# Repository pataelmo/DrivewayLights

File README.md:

# DrivewayLights
This is a project to create smart IoT driveway lights.

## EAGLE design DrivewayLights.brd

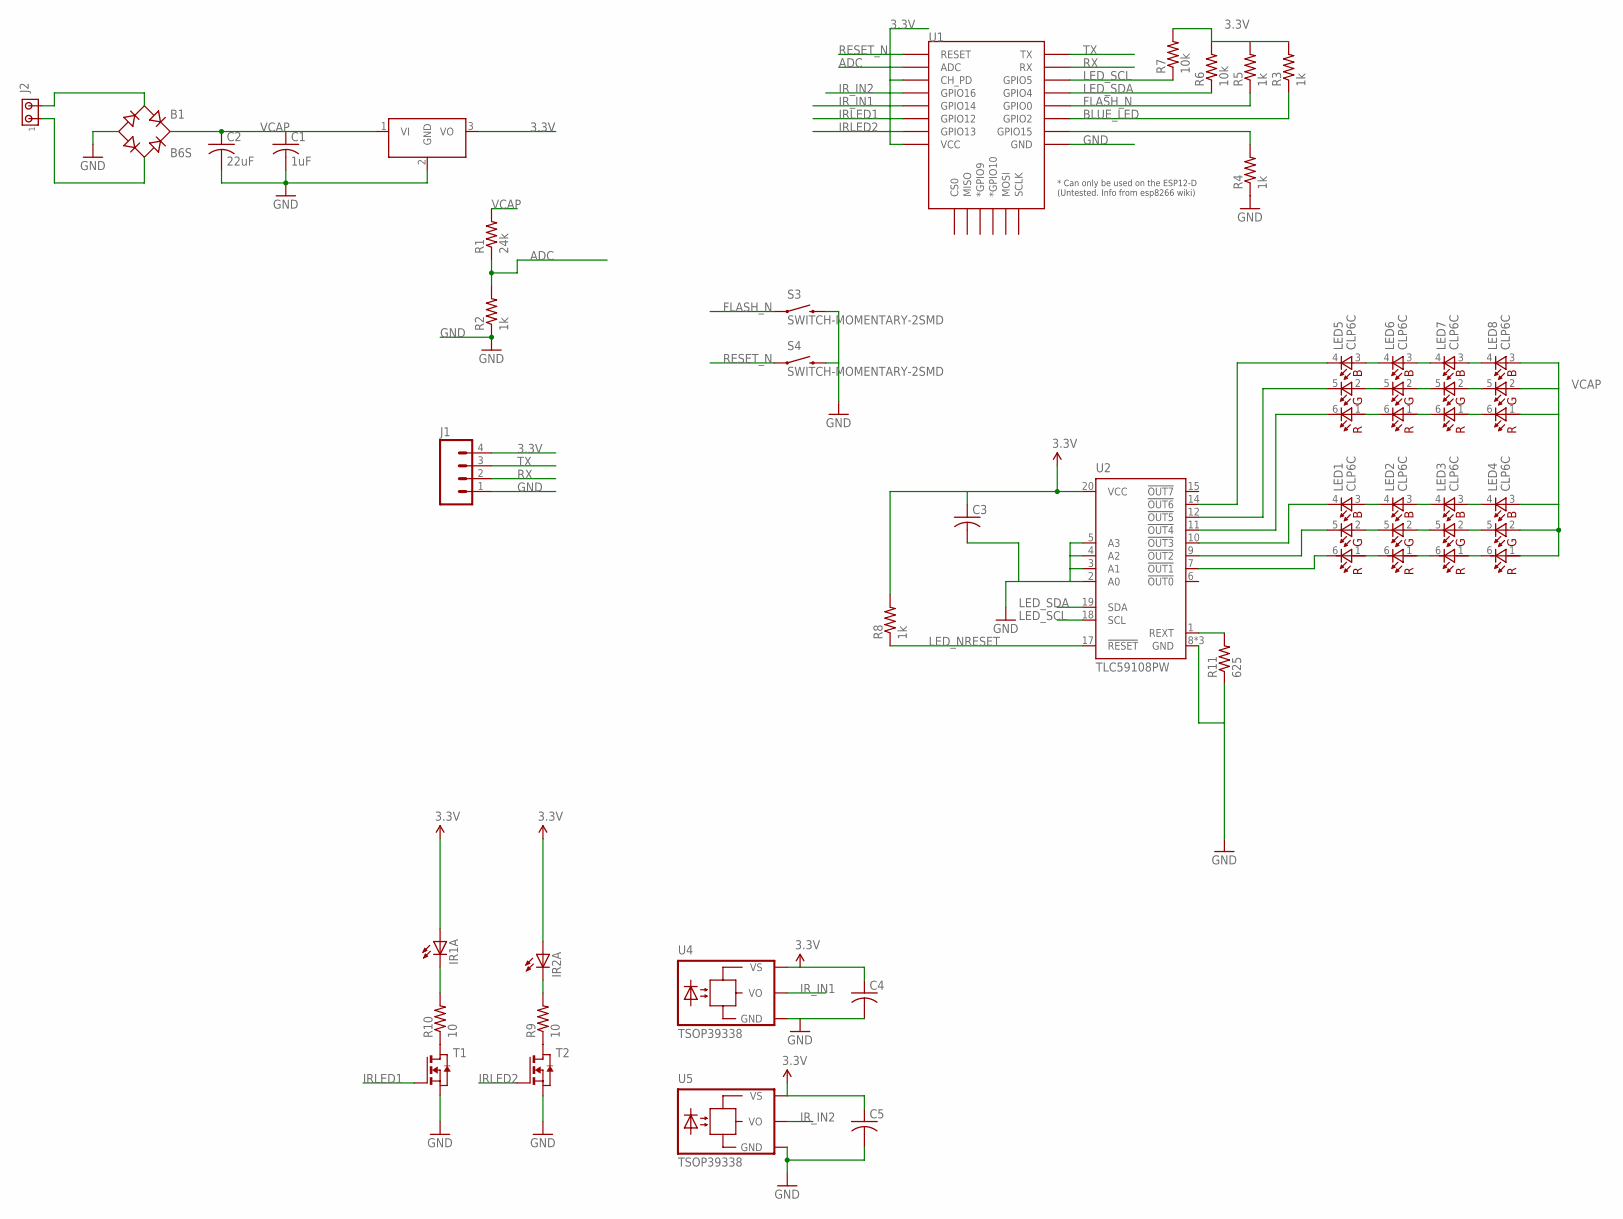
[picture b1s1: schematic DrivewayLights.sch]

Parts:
B1: B6S; MBS
C1: 1uF; C0805
C2: 22uF; C1210
C3, C4, C5: C-USC0603; C0603
IR1A, IR2A: LED5MM
J1: M04JST-PTH-VERT; JST-4-PTH-VERT
J2: MTA02-100; 10X02MTA
LED1, LED2, LED3, LED4, LED5, LED6, LED7, LED8: CLP6C
R1: 24k; R0603
R2, R3, R4, R5, R8: 1k; R0603
R6, R7: 10k; R0603
R9, R10: 10; R0603
R11: 625; R0603
S3, S4: SWITCH-MOMENTARY-2SMD; TACTILE-SWITCH-SMD
T1, T2: NMOSSOT23; SOT-23
U1: ESP12ESMD; ESP12E-SMD
U2: TLC59108PW; PW_R-PDSO-G20
U3: DCDC_OKI-78SR; OKI-78SRH
U4, U5: TSOP39338

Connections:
3.3V: C3.1, C4.1, C5.1, IR1A.A, IR2A.A, J1.4, R3.2, R5.2, R6.2, R7.2, R8.2, U1.CH_PD, U1.VCC, U2.20 (VCC), U3.3 (VO), U4.VS, U5.VS
ADC: R1.1, R2.2, U1.ADC
BLUE: LED1.4 (BC), U2.10 (!OUT3)
BLUE2: LED5.4 (BC), U2.14 (!OUT6)
BLUE_LED: R3.1, U1.GPIO2
FLASH_N: R5.1, S3.1, U1.GPIO0
GND: B1.-, C1.2, C2.2, C3.2, C4.2, C5.2, J1.1, R2.1, R4.1, R11.1, S3.3 (2), S4.3 (2), T1.2 (S), T2.2 (S), U1.GND, U2.2 (A0), U2.3 (A1), U2.4 (A2), U2.5 (A3), U2.8 (GND), U2.13 (GND), U2.16 (GND), U3.2 (GND), U4.GND, U5.GND
GREEN: LED1.5 (GC), U2.9 (!OUT2)
GREEN2: LED5.5 (GC), U2.12 (!OUT5)
IRLED0: R4.2, U1.GPIO15
IRLED1: T1.3 (G), U1.GPIO12
IRLED2: T2.3 (G), U1.GPIO13
IR_IN1: U1.GPIO14, U4.OUT (VO)
IR_IN2: U1.GPIO16, U5.OUT (VO)
LED_CURRENT_R: R11.2, U2.1 (REXT)
LED_NRESET: R8.1, U2.17 (!RESET)
LED_SCL: R7.1, U1.GPIO5, U2.18 (SCL)
LED_SDA: R6.1, U1.GPIO4, U2.19 (SDA)
unnamed: IR2A.K (C), R9.2
unnamed: IR1A.K (C), R10.2
unnamed: R10.1, T1.1 (D)
unnamed: R9.1, T2.1 (D)
unnamed: LED5.3 (BA), LED6.4 (BC)
unnamed: LED6.3 (BA), LED7.4 (BC)
unnamed: LED7.3 (BA), LED8.4 (BC)
unnamed: LED7.2 (GA), LED8.5 (GC)
unnamed: LED6.2 (GA), LED7.5 (GC)
unnamed: LED5.2 (GA), LED6.5 (GC)
unnamed: LED5.1 (RA), LED6.6 (RC)
unnamed: LED6.1 (RA), LED7.6 (RC)
unnamed: LED7.1 (RA), LED8.6 (RC)
unnamed: LED1.3 (BA), LED2.4 (BC)
unnamed: LED2.3 (BA), LED3.4 (BC)
unnamed: LED3.3 (BA), LED4.4 (BC)
unnamed: LED3.2 (GA), LED4.5 (GC)
unnamed: LED2.2 (GA), LED3.5 (GC)
unnamed: LED1.2 (GA), LED2.5 (GC)
unnamed: LED1.1 (RA), LED2.6 (RC)
unnamed: LED2.1 (RA), LED3.6 (RC)
unnamed: LED3.1 (RA), LED4.6 (RC)
unnamed: B1.AC1, J2.2
unnamed: B1.AC2, J2.1
RED: LED1.6 (RC), U2.7 (!OUT1)
RED2: LED5.6 (RC), U2.11 (!OUT4)
RESET_N: S4.1, U1.RESET
RX: J1.2, U1.RXD0 (RX)
TX: J1.3, U1.TXD0 (TX)
VCAP: B1.+, C1.1, C2.1, LED4.1 (RA), LED4.2 (GA), LED4.3 (BA), LED8.1 (RA), LED8.2 (GA), LED8.3 (BA), R1.2, U3.1 (VI)

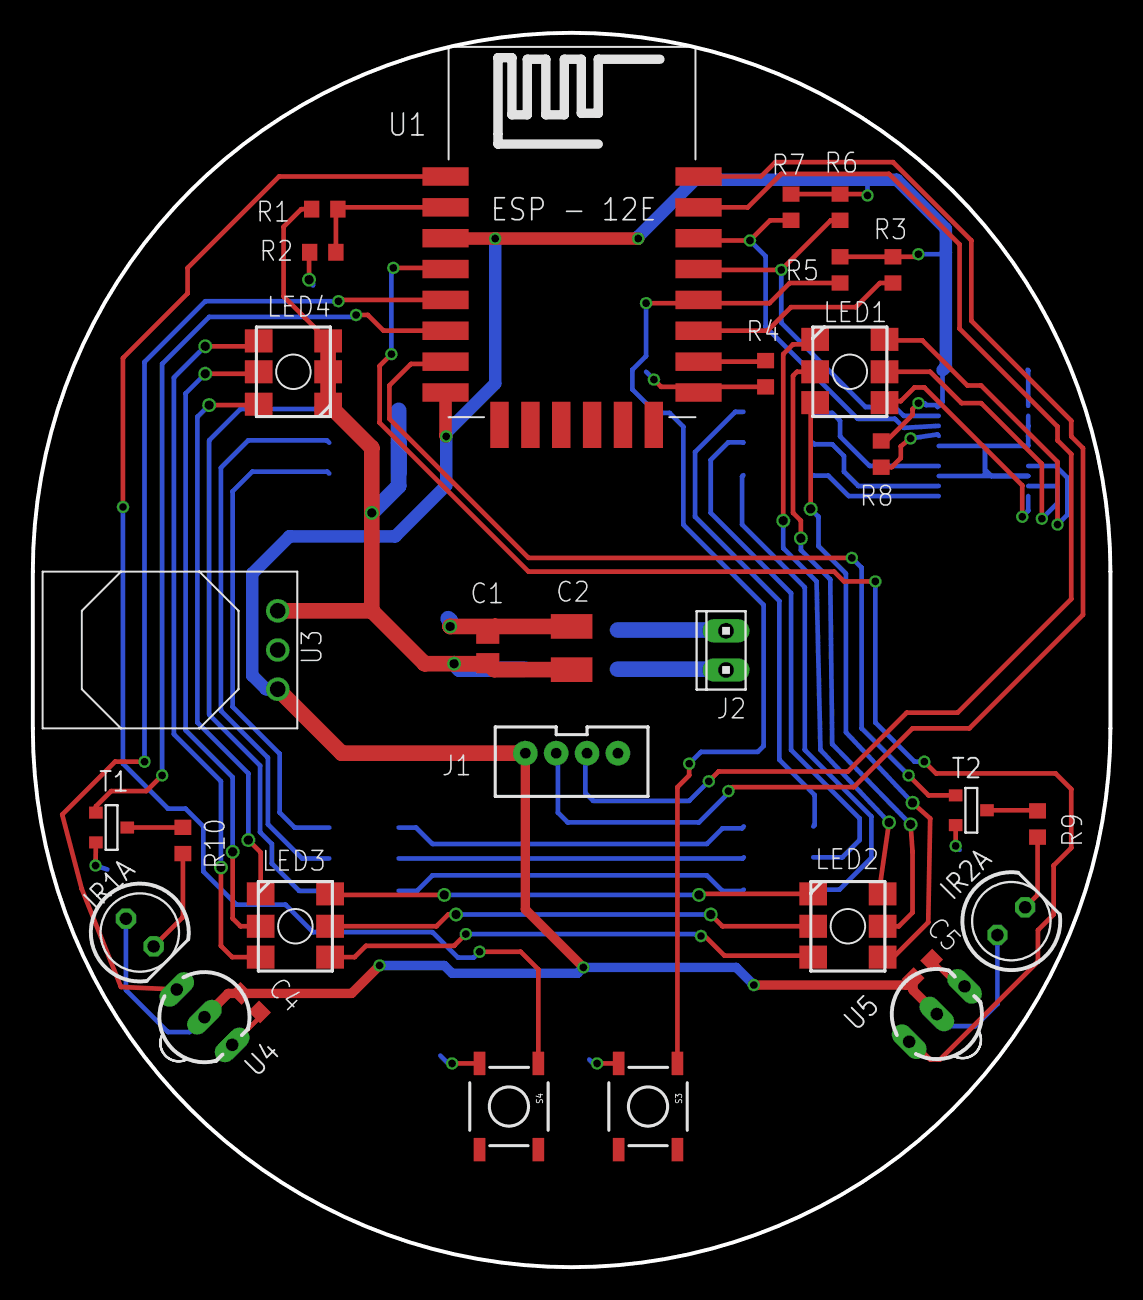
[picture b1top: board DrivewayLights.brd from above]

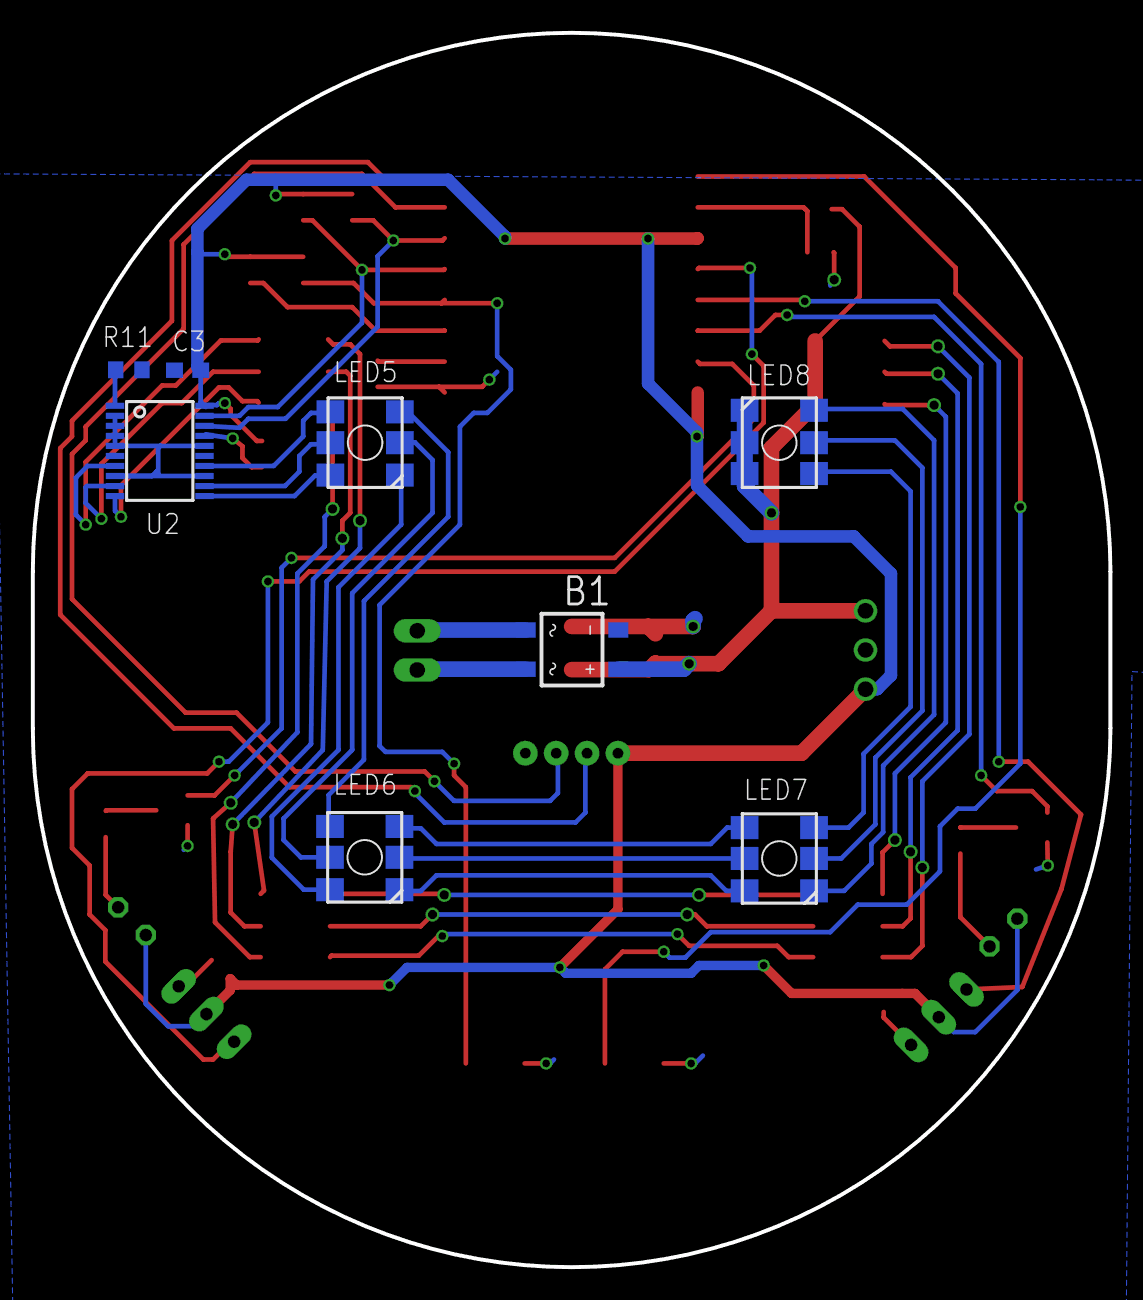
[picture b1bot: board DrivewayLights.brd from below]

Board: 2 copper layers, 69.8 x 80.0 mm, 38 parts (8 on the bottom side), 48 nets.

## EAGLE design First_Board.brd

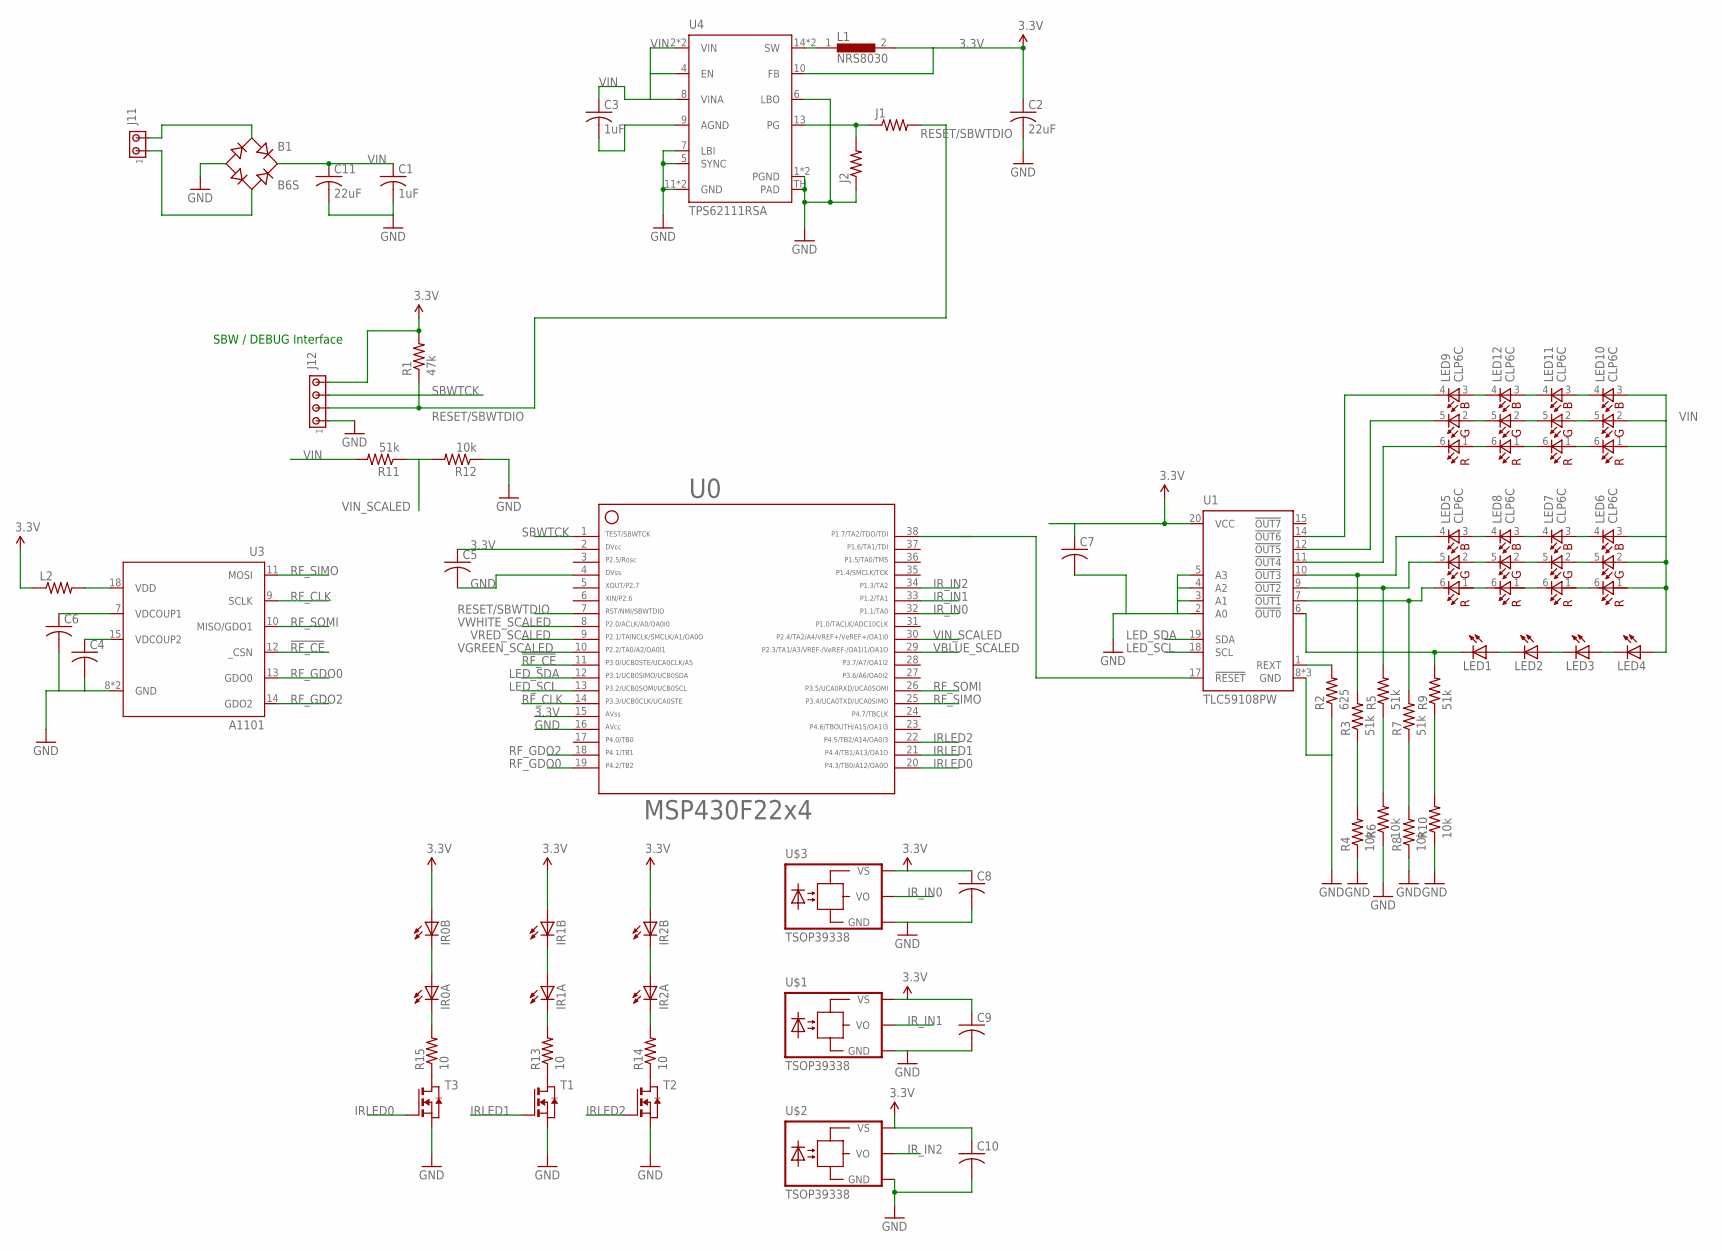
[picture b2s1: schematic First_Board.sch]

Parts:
B1: B6S; MBS
C1: 1uF; C0805
C2: 22uF; C0805
C3: 1uF; C0603
C4, C5, C6, C7, C8, C9, C10: C-USC0603; C0603
C11: 22uF; C1210
IR0A, IR0B, IR1A, IR1B, IR2A, IR2B: LED5MM
J1, J2: R-US_R0603; R0603
J11: MTA02-100; 10X02MTA
J12: MTA04-100; 10X04MTA
L1: NRS8030
L2: R-US_R0603; R0603
LED1, LED2, LED3, LED4: LED-2AC-SUPERFLUX; SUPERFLUX-7.6X7.6
LED5, LED6, LED7, LED8, LED9, LED10, LED11, LED12: CLP6C
R1: 47k; R0603
R2: 625; R0603
R3, R5, R7, R9, R11: 51k; R0603
R4, R6, R8, R10, R12: 10k; R0603
R13, R14, R15: 10; R0603
T1, T2, T3: NMOSSOT23; SOT-23
U0: F22X4---DA38; DA38
U1: TLC59108PW; PW_R-PDSO-G20
U3: A1101
U4: TPS62111RSA; S-PVQFN-N16
U$1, U$2, U$3: TSOP39338

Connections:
3.3V: C2.1, C5.1, C7.1, C8.1, C9.1, C10.1, IR0B.A, IR1B.A, IR2B.A, J12.4, L1.2, L2.1, R1.2, U0.2, U0.15, U1.20 (VCC), U4.10 (FB), U$1.VS, U$2.VS, U$3.VS
!RF_CE: U0.11, U3.12 (_CSN)
BLUE: LED5.4 (BC), R3.2, U1.10 (!OUT3)
BLUE2: LED9.4 (BC), U1.14 (!OUT6)
GND: B1.-, C1.2, C2.2, C4.2, C5.2, C6.2, C7.2, C8.2, C9.2, C10.2, C11.2, J2.1, J12.1, R2.1, R4.1, R6.1, R8.1, R10.1, R12.1, T1.2 (S), T2.2 (S), T3.2 (S), U0.4, U0.16, U1.2 (A0), U1.3 (A1), U1.4 (A2), U1.5 (A3), U1.8 (GND), U1.13 (GND), U1.16 (GND), U3.8 (GND), U3.17 (GND), U4.1 (PGND), U4.5 (SYNC), U4.6 (LBO), U4.7 (LBI), U4.11 (GND), U4.12 (GND), U4.16 (PGND), U4.TH (PAD), U$1.GND, U$2.GND, U$3.GND
GREEN: LED5.5 (GC), R5.2, U1.9 (!OUT2)
GREEN2: LED9.5 (GC), U1.12 (!OUT5)
IRLED0: T3.3 (G), U0.20
IRLED1: T1.3 (G), U0.21
IRLED2: T2.3 (G), U0.22
IR_IN0: U0.32, U$3.OUT (VO)
IR_IN1: U0.33, U$1.OUT (VO)
IR_IN2: U0.34, U$2.OUT (VO)
LED_SCL: U0.13, U1.18 (SCL)
LED_SDA: U0.12, U1.19 (SDA)
unnamed: L1.1, U4.14 (SW), U4.15 (SW)
unnamed: IR2A.K (C), R14.2
unnamed: IR2A.A, IR2B.K (C)
unnamed: IR1A.A, IR1B.K (C)
unnamed: IR1A.K (C), R13.2
unnamed: R13.1, T1.1 (D)
unnamed: C3.2, U4.9 (AGND)
unnamed: R14.1, T2.1 (D)
unnamed: LED1.1 (C), LED1.3 (C), R9.2, U1.6 (!OUT0)
unnamed: LED9.3 (BA), LED12.4 (BC)
unnamed: LED11.4 (BC), LED12.3 (BA)
unnamed: LED10.4 (BC), LED11.3 (BA)
unnamed: LED10.5 (GC), LED11.2 (GA)
unnamed: LED11.5 (GC), LED12.2 (GA)
unnamed: LED9.2 (GA), LED12.5 (GC)
unnamed: LED9.1 (RA), LED12.6 (RC)
unnamed: R2.2, U1.1 (REXT)
unnamed: LED11.6 (RC), LED12.1 (RA)
unnamed: LED10.6 (RC), LED11.1 (RA)
unnamed: IR0A.K (C), R15.2
unnamed: IR0A.A, IR0B.K (C)
unnamed: R15.1, T3.1 (D)
unnamed: LED5.3 (BA), LED8.4 (BC)
unnamed: LED7.4 (BC), LED8.3 (BA)
unnamed: LED6.4 (BC), LED7.3 (BA)
unnamed: LED6.5 (GC), LED7.2 (GA)
unnamed: LED7.5 (GC), LED8.2 (GA)
unnamed: LED5.2 (GA), LED8.5 (GC)
unnamed: LED5.1 (RA), LED8.6 (RC)
unnamed: LED7.6 (RC), LED8.1 (RA)
unnamed: LED6.6 (RC), LED7.1 (RA)
unnamed: LED1.2 (A), LED1.4 (A), LED2.1 (C), LED2.3 (C)
unnamed: LED2.2 (A), LED2.4 (A), LED3.1 (C), LED3.3 (C)
unnamed: LED3.2 (A), LED3.4 (A), LED4.1 (C), LED4.3 (C)
unnamed: B1.AC1, J11.2
unnamed: B1.AC2, J11.1
unnamed: L2.2, U3.18 (VDD)
PG: J1.1, J2.2, U4.13 (PG)
RED: LED5.6 (RC), R7.2, U1.7 (!OUT1)
RED2: LED9.6 (RC), U1.11 (!OUT4)
RESET/SBWTDIO: J1.2, J12.2, R1.1, U0.7
RF_CLK: U0.14, U3.9 (SCLK)
RF_GDO0: U0.19, U3.13 (GDO0)
RF_GDO2: U0.18, U3.14 (GDO2)
RF_SIMO: U0.25, U3.11 (MOSI)
RF_SOMI: U0.26, U3.10 (MISO/GDO1)
SBWTCK: J12.3, U0.1
VBLUE_SCALED: R3.1, R4.2, U0.29
VDCOUP1: C6.1, U3.7 (VDCOUP1)
VDCOUP2: C4.1, U3.15 (VDCOUP2)
VGREEN_SCALED: R5.1, R6.2, U0.10
VIN: B1.+, C1.1, C3.1, C11.1, LED4.2 (A), LED4.4 (A), LED6.1 (RA), LED6.2 (GA), LED6.3 (BA), LED10.1 (RA), LED10.2 (GA), LED10.3 (BA), R11.2, U4.2 (VIN), U4.3 (VIN), U4.4 (EN), U4.8 (VINA)
VIN_SCALED: R11.1, R12.2, U0.30
VRED_SCALED: R7.1, R8.2, U0.9
VWHITE_SCALED: R9.1, R10.2, U0.8

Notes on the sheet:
SBW / DEBUG Interface

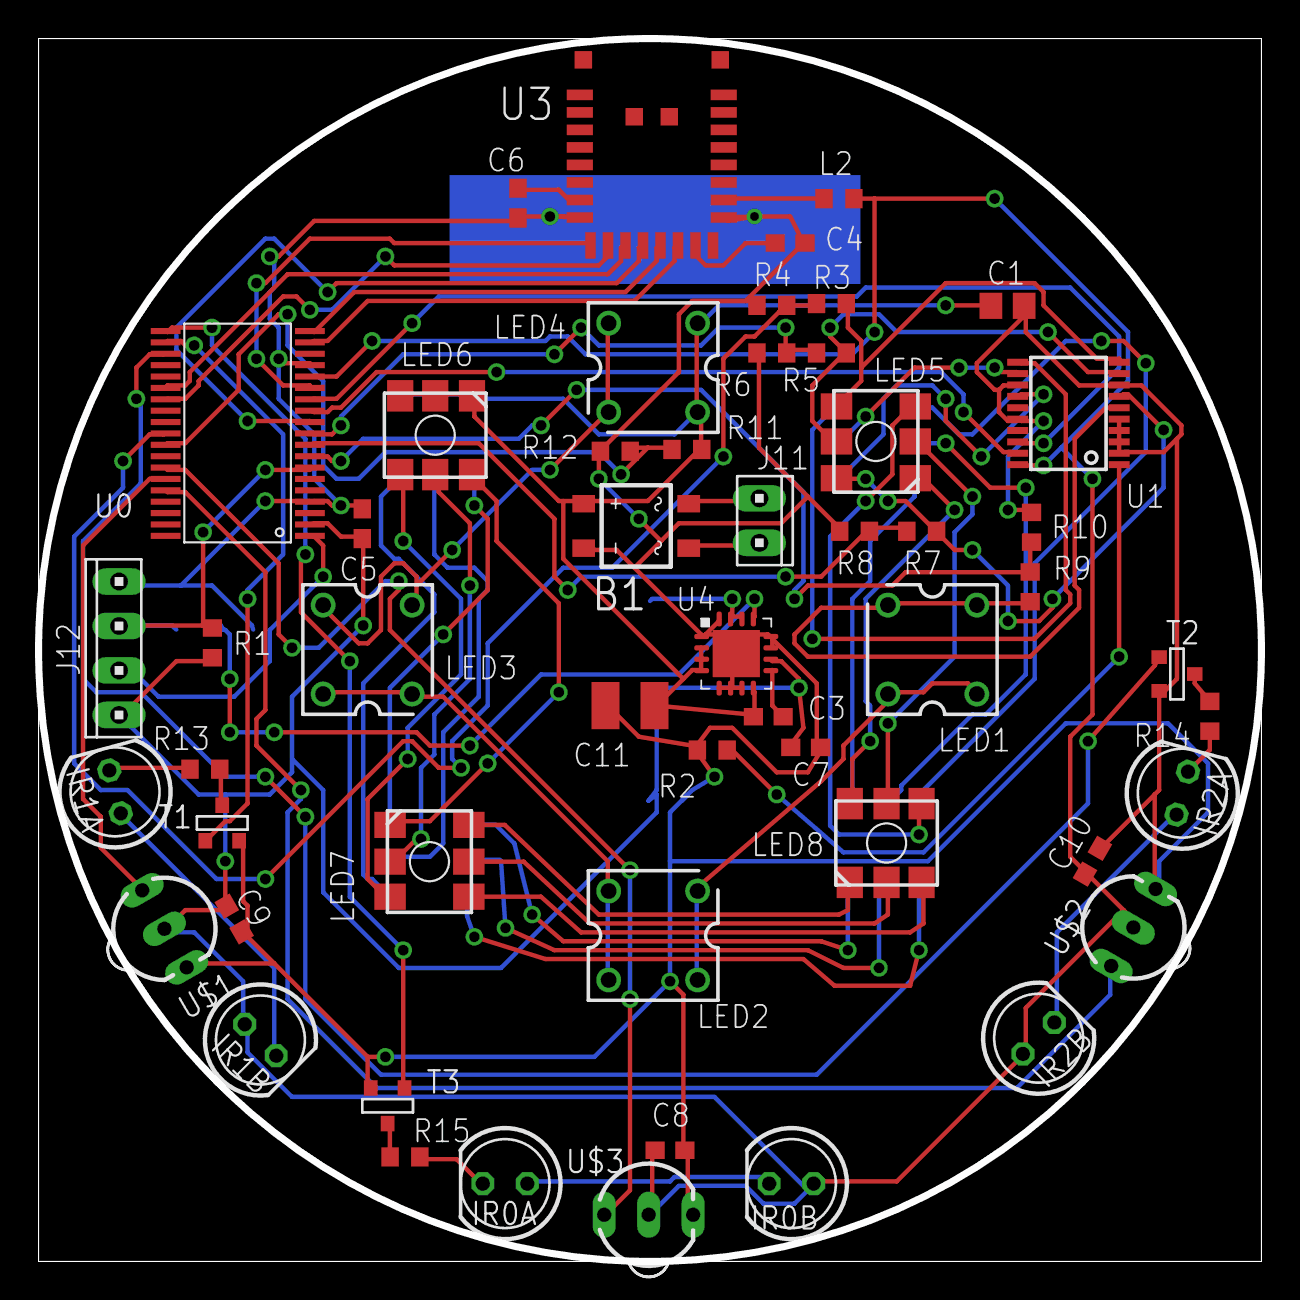
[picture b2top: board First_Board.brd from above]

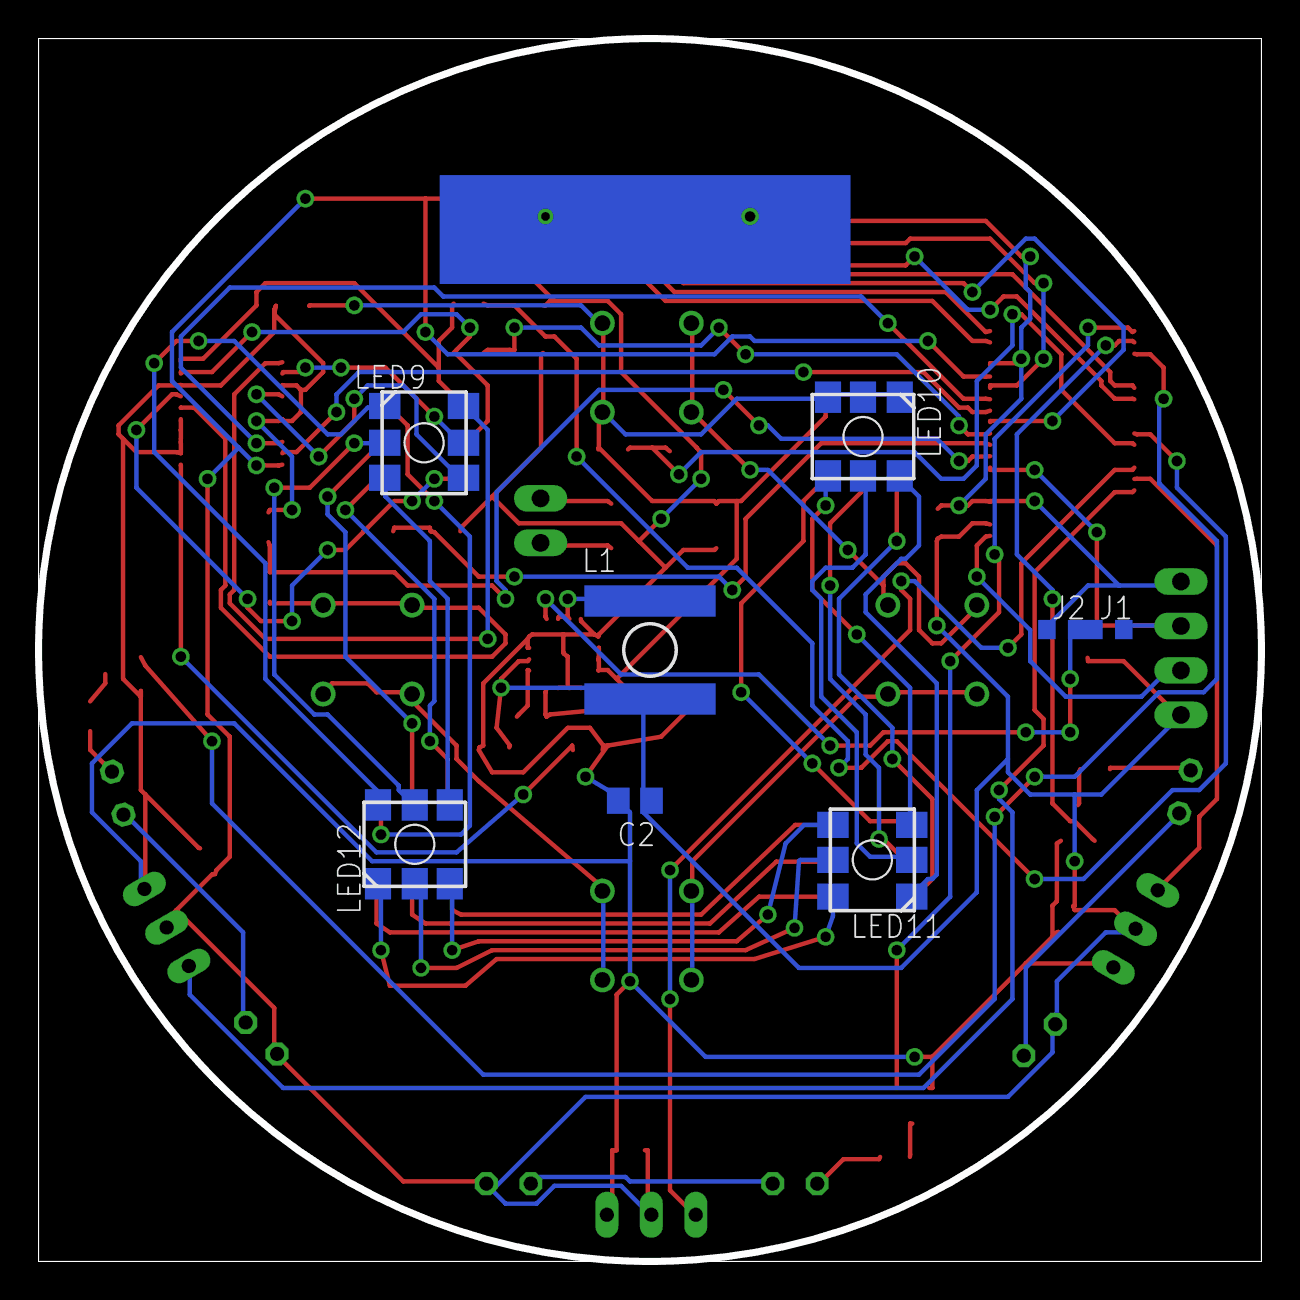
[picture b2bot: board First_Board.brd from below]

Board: 2 copper layers, 69.9 x 69.9 mm, 61 parts (8 on the bottom side), 70 nets.

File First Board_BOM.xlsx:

Designator | Type | Value | Part # | Package |  | ORDER
J11 | Connector | Power In |  | 2 Pin |  | ???
B1 | Bridge | - | B6S
C11 | Capacitor | 22uF |  | 1210
C1 | Capacitor | 1uF |  | 0805
U4 | IC | - | TPS62111RSA | PVQFN-16
C3 | Capacitor | 1uF |  | 0603
L1 | Inductor | - | NRS8030
J1/J2 | Resistor | 0 |  | 0603
C2 | Capacitor | 22uF |  | 0805
J12 | Connector | JTAG |  | 4 Pin
R1 | Resistor | 47k |  | 0603
R11 | Resistor | 51k |  | 0603
R12 | Resistor | 10k |  | 0603
U3 | Module | - | A1101
L2 | Inductor | - |  | 0603 |  | 0 ohm
C6 | Capacitor | - |  | 0603 |  | NO
C4 | Capacitor | - |  | 0603 |  | NO
U0 | IC | - | MSP430F2274 | DA38?
C5 | Capacitor | 1uF |  | 0603 |  | 1uF
U1 | IC | - | TLC59108PW
C7 | Capacitor | 1uF |  | 0603 |  | 1uF
R2 | Resistor | 625 |  | 0603
R3 | Resistor | 51k |  | 0603
R4 | Resistor | 10k |  | 0603
R5 | Resistor | 51k |  | 0603
R6 | Resistor | 10k |  | 0603
R7 | Resistor | 51k |  | 0603
R8 | Resistor | 10k |  | 0603
R9 | Resistor | 51k |  | 0603
R10 | Resistor | 10k |  | 0603
LED1-4 | LED | White | 7.6
LED5-12 | LED | RGB | CLP6C
IR0A-B | LED | IR
IR1A-B | LED | IR
IR2A-B | LED | IR
R13-R15 | Resistor | 10 |  | 0603
T1-T3 | FET | NMOS |  | SOT23
U$1-U$3 | IC | - | TSOP39338
C8-C10 | Capacitor | 1uF |  | 0603

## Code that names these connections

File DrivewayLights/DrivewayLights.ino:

#include <TLC59108.h>
#include <ESP8266WiFi.h>
#include <WiFiUdp.h>
#include <Wire.h>

//#define HW_RESET_PIN 16
#define LED_SCL_PIN 5
#define LED_SDA_PIN 4
//#define IRLED1_PIN  12
//#define IRLED2_PIN  13
//#define IRIN1_PIN   16
//#define IRIN2_PIN   5
#define BLUE_LED  2
#define RED_LED  16

#define I2C_ADDR TLC59108::I2C_ADDR::BASE
#define LED_CURRENT_GAIN_VALUE  0xD5

TLC59108 leds(0x40);
WiFiUDP Udp;
unsigned int localUdpPort = 4210;
char incomingPacket[255];
char  replyPacekt[] = "Hi there! Got the message :-)";
int lastTime = 0;
bool blinkOn = false;
int cycleCount = 0;
const uint8_t allOn[8] = {255,255,255,255,255,255,255,255};
const uint8_t allOff[8] = {0,0,0,0,0,0,0,0};


void setup() {
    // put your setup code here, to run once:
    Serial.begin(115200);
    Serial.println();
    Wire.begin(LED_SDA_PIN, LED_SCL_PIN);
    Wire.setClock(50000L);
    pinMode(RED_LED,OUTPUT);
    pinMode(BLUE_LED,OUTPUT);
    digitalWrite(RED_LED,1);
    digitalWrite(BLUE_LED,0);
    leds.init();
    leds.setLedOutputMode(TLC59108::LED_MODE::PWM_IND);
    leds.setRegister(TLC59108::REGISTER::IREF::ADDR, LED_CURRENT_GAIN_VALUE);
    leds.setAllBrightness((uint8_t)0);
    WiFi.begin("<SSID>","<password>");
    
      while(WiFi.status() != WL_CONNECTED)
      {
          delay(250);
          if(blinkOn)
        {
          digitalWrite(BLUE_LED,1);
        }
        else
        {
          digitalWrite(BLUE_LED,0);
        }
        blinkOn = !blinkOn;
      }
    Udp.begin(localUdpPort);
    Serial.printf("Now listening at IP %s, UDP port %d\n", WiFi.localIP().toString().c_str(), localUdpPort);
}

void loop() {
    // put your main code here, to run repeatedly:
    int packetSize = Udp.parsePacket();
    if (packetSize)
    {
      //Serial.printf("Received %d bytes from %s, port %d\n", packetSize, Udp.remoteIP().toString().c_str(), Udp.remotePort());
      int len = Udp.read(incomingPacket, 255);
      if (len > 0)
      {
        incomingPacket[len] = 0;
        if ((incomingPacket[0] == 0x70) && (len > 2)) {
          leds.setBrightness(incomingPacket[1],incomingPacket[2]);
        }
      }
      Udp.beginPacket(Udp.remoteIP(), Udp.remotePort());
        Udp.write(replyPacekt);
        Udp.endPacket();
    }
    if (millis()-lastTime > 1000)
    {
      lastTime = millis();
//      Serial.print("S:");
//      Serial.println(WiFi.RSSI());
//      Udp.beginPacket("10.33.33.255", localUdpPort);
//        Udp.write("RSSI=");
//        Udp.write(WiFi.RSSI());
        
//           if(cycleCount == 0) {
//              leds.setBrightness(1,10);
//           } else if (cycleCount == 1) {
//              leds.setBrightness(2,10);
//           } else if (cycleCount == 2) {
//              leds.setBrightness(3,10);
//           } else if (cycleCount == 3) {
//              leds.setBrightness(1,0);
//           } else if (cycleCount == 4) {
//              leds.setBrightness(2,0);
//           } else if (cycleCount == 5) {
//              leds.setBrightness(3,0);
//           } 
//           cycleCount++;
//           if (cycleCount > 5) {cycleCount = 0;}
        if(blinkOn)
        {
          digitalWrite(RED_LED,1);
        }
        else
        {
          digitalWrite(RED_LED,0);
        }
        blinkOn = !blinkOn;
//        Udp.endPacket();
    }
}

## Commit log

2011-12-24 Adding driveway light boards
2011-12-27 Updated to add IR
2011-12-28 Adding bypass caps
2012-01-01 Adding IR LED/Detector (and maybe the bottom RGB leds if not already committed
2012-01-04 Updated to add labels to nets
2012-01-13 Adding rectifier bridge to schematic
2012-01-13 Schematic review with V
2012-01-14 Placed changes from schematic update, some manual routing, but mostly autorouted board
2012-01-27 Updates?
2012-04-20 DRC Fixes, moved name labels so they won't overlap exposed copper
2013-08-05 New version of Eagle... also adding BOM
2013-09-14 Adding zip file (what was used to generate the first boards?) adding first rework file
2013-09-14 Resized rework1 to fit on a page and created a pdf
2016-07-26 Removing backup files
2016-07-26 Changing to using a better file name.
2016-07-26 Updating BOM name and removing unneeded rework from older version.
2016-07-26 First pass at adding the Photon board
2016-07-26 Some layout cleanup
2016-09-22 Updated Board design to test new size to just fit into bottom bulge. Adding 3d models
2016-09-28 Changed to using ESP8266 board and started laying out board.
2016-09-28 Updated to a fully routed board. Could have some bugs, needs electrical and mechanical review
2016-09-28 Updated 3d model data to give more complete 3d model
2016-09-29 Updates to schematic and board layout - a lot of signals ripped up for using correct footprint and adding buttons and interface for programming.
2016-10-04 Changed LED routing a bit to help route other traces.
2016-10-04 Added some missing connections on schematic and did some more manual routing
2016-10-13 Updates to board layout to bring dimensions back into where they should probably be. Need to route board again, but hopefully this will now be good assuming the schematic is right. Also capturing las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
2016-10-13 Adding basic test arduino sketch to control LEDs over wifi
2016-10-16 Updates to schematic and relayout board
2016-10-20 Renamed parts and cleaned up silkscreen on board to prepare for next build
2016-10-28 fixed board outline issue and adding Gerber's
2016-10-31 Forgot to move the drill (.TXT) file into the gerber folder.

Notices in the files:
parts and their libraries:
SparkFun-Electromechanical: Licensing: Creative Commons ShareAlike 4.0 International - https://creativecommons.org/licenses/by-sa/4.0
SparkFun: Licensing: CC v3.0 Share-Alike You are welcome to use this library for commercial purposes.
